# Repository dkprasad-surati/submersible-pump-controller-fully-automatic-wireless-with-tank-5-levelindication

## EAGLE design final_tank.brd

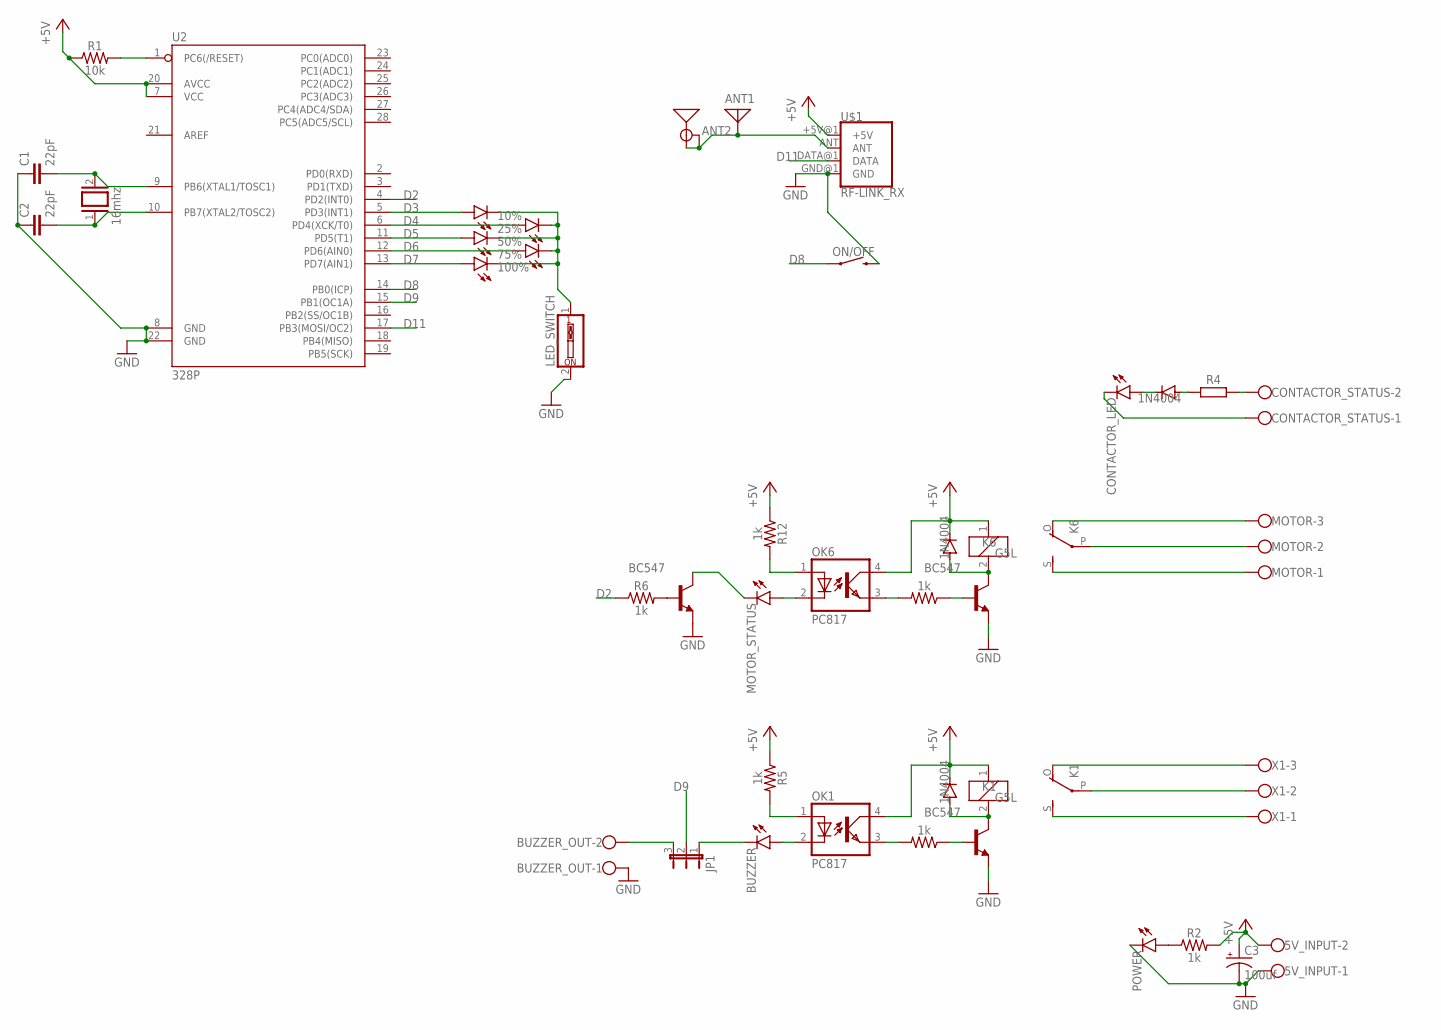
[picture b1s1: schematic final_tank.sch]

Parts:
5V_INPUT: W237-102
10%, 25%, 50%, 75%, 100%: LED3MM
ANT1: ANTENNA; PAD-01
ANT2: ANTENNA-GROUNDEDTRACE-15.2MM; TRACE_ANTENNA_2.4GHZ_15.2MM
BUZZER: LED3MM
BUZZER_OUT: W237-102
C1, C2: 22pF; CAP-PTH-2.54
C3: 100uf; CPOL-RADIAL-5MM-10MM
CONTACTOR_LED: LED3MM
CONTACTOR_STATUS: W237-102
D1, D2, D6: 1N4004; DO41-10
JP1: JP2E; JP2
K1, K6: G5L; G5LE
LED_SWITCH: SW_DIP-1; EDG-01
MOTOR: W237-103
MOTOR_STATUS: LED3MM
OK1, OK6: PC817; DIL04
ON/OFF: MOMENTARY-SWITCH-SPST-PTH-6.0MM; TACTILE_SWITCH_PTH_6.0MM
POWER: LED3MM
Q1: 16mhz; QS
R1: 10k; AXIAL-0.3
R2, R3, R5, R6, R11, R12: 1k; AXIAL-0.3
R4: R_AXIAL-11.7MM-PITCH; RESAD1176W63L850D250B
T1, T2, T6: BC547; TO92
U2: 328P; DIP28
U$1: RF-LINK_RX
X1: W237-103

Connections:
+5V: 5V_INPUT.2, C3.+, R1.P$1 (1), R2.P$2 (2), U2.7 (VCC), U2.20 (AVCC), U$1.+5V@1 (+5V)
D2: R6.P$1 (1), U2.4 (PD2(INT0))
D3: 10%.A, U2.5 (PD3(INT1))
D4: 25%.A, U2.6 (PD4(XCK/T0))
D5: 50%.A, U2.11 (PD5(T1))
D6: 75%.A, U2.12 (PD6(AIN0))
D7: 100%.A, U2.13 (PD7(AIN1))
D8: ON/OFF.1, U2.14 (PB0(ICP))
D9: JP1.2, U2.15 (PB1(OC1A))
D11: U2.17 (PB3(MOSI/OC2)), U$1.DATA@1 (DATA)
GND: 5V_INPUT.1, BUZZER_OUT.1, C1.1, C2.1, C3.-, LED_SWITCH.2, ON/OFF.3 (2), POWER.K (C), T1.1 (E), T2.1 (E), T6.1 (E), U2.8 (GND), U2.22 (GND), U$1.GND@1 (GND)
unnamed: R1.P$2 (2), U2.1 (PC6(/RESET))
unnamed: C1.2, Q1.2, U2.9 (PB6(XTAL1/TOSC1))
unnamed: C2.2, Q1.1, U2.10 (PB7(XTAL2/TOSC2))
unnamed: K6.P, MOTOR.2
unnamed: POWER.A, R2.P$1 (1)
unnamed: D2.C, D6.C, K1.1, K6.1, OK1.4 (COL), OK6.4 (COL), R5.P$1 (1), R12.P$1 (1)
unnamed: D1.A, R4.1
unnamed: CONTACTOR_LED.A, D1.C
unnamed: CONTACTOR_STATUS.2, R4.2
unnamed: CONTACTOR_LED.K (C), CONTACTOR_STATUS.1
unnamed: 10%.K (C), 25%.K (C), 50%.K (C), 75%.K (C), 100%.K (C), LED_SWITCH.1
unnamed: ANT1.1, ANT2.ANT (SIGNAL), ANT2.GND, U$1.ANT
unnamed: D2.A, K1.2, T1.3 (C)
unnamed: R3.P$1 (1), T1.2 (B)
unnamed: OK1.3 (EMIT), R3.P$2 (2)
unnamed: BUZZER.A, OK1.2 (C)
unnamed: OK1.1 (A), R5.P$2 (2)
unnamed: K1.O, X1.3
unnamed: K1.S, X1.1
unnamed: K1.P, X1.2
unnamed: R6.P$2 (2), T2.2 (B)
unnamed: MOTOR_STATUS.K (C), T2.3 (C)
unnamed: BUZZER_OUT.2, JP1.3
unnamed: BUZZER.K (C), JP1.1
unnamed: D6.A, K6.2, T6.3 (C)
unnamed: R11.P$1 (1), T6.2 (B)
unnamed: OK6.3 (EMIT), R11.P$2 (2)
unnamed: MOTOR_STATUS.A, OK6.2 (C)
unnamed: OK6.1 (A), R12.P$2 (2)
unnamed: K6.O, MOTOR.3
unnamed: K6.S, MOTOR.1

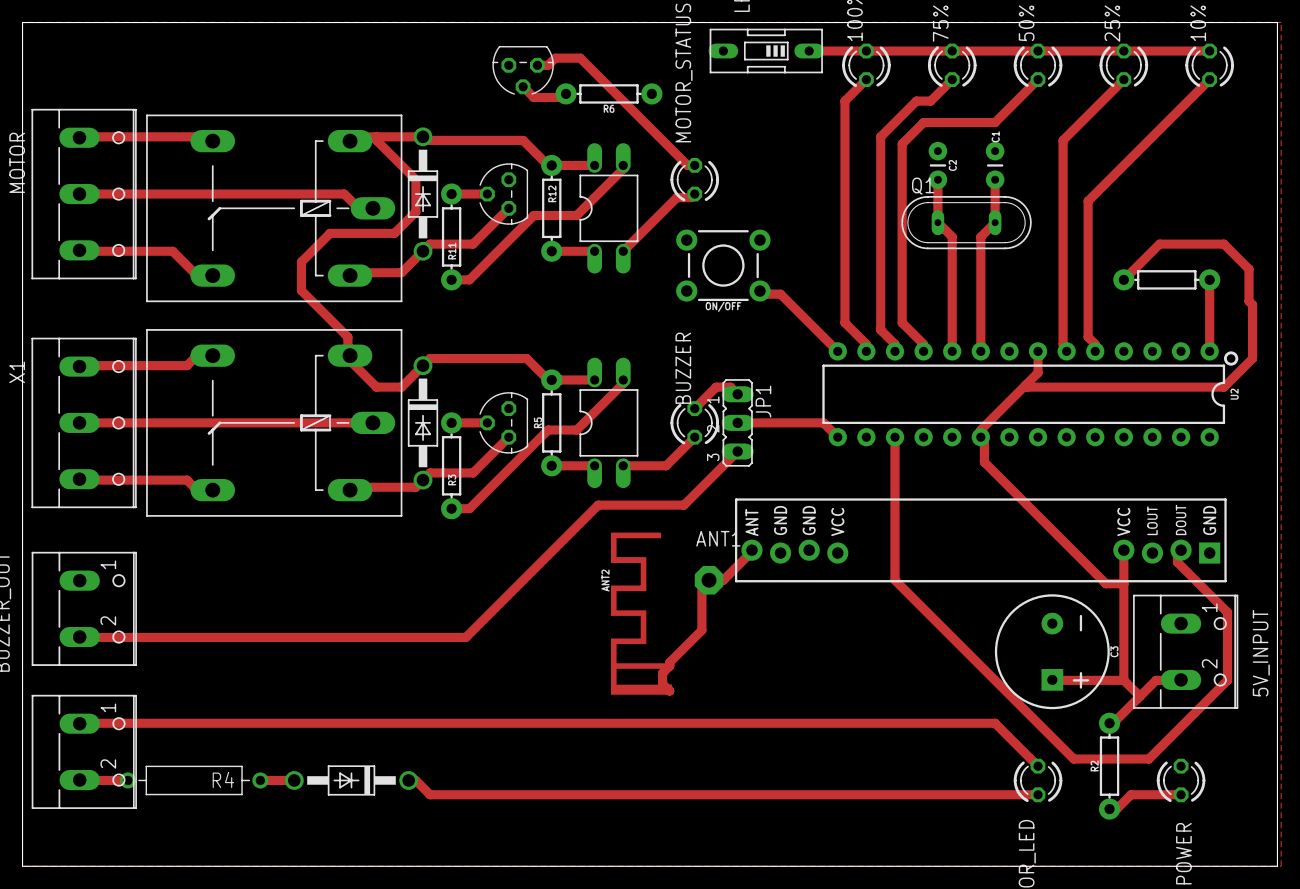
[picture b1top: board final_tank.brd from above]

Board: 2 copper layers, 111.4 x 74.9 mm, 43 parts (0 on the bottom side), 42 nets.

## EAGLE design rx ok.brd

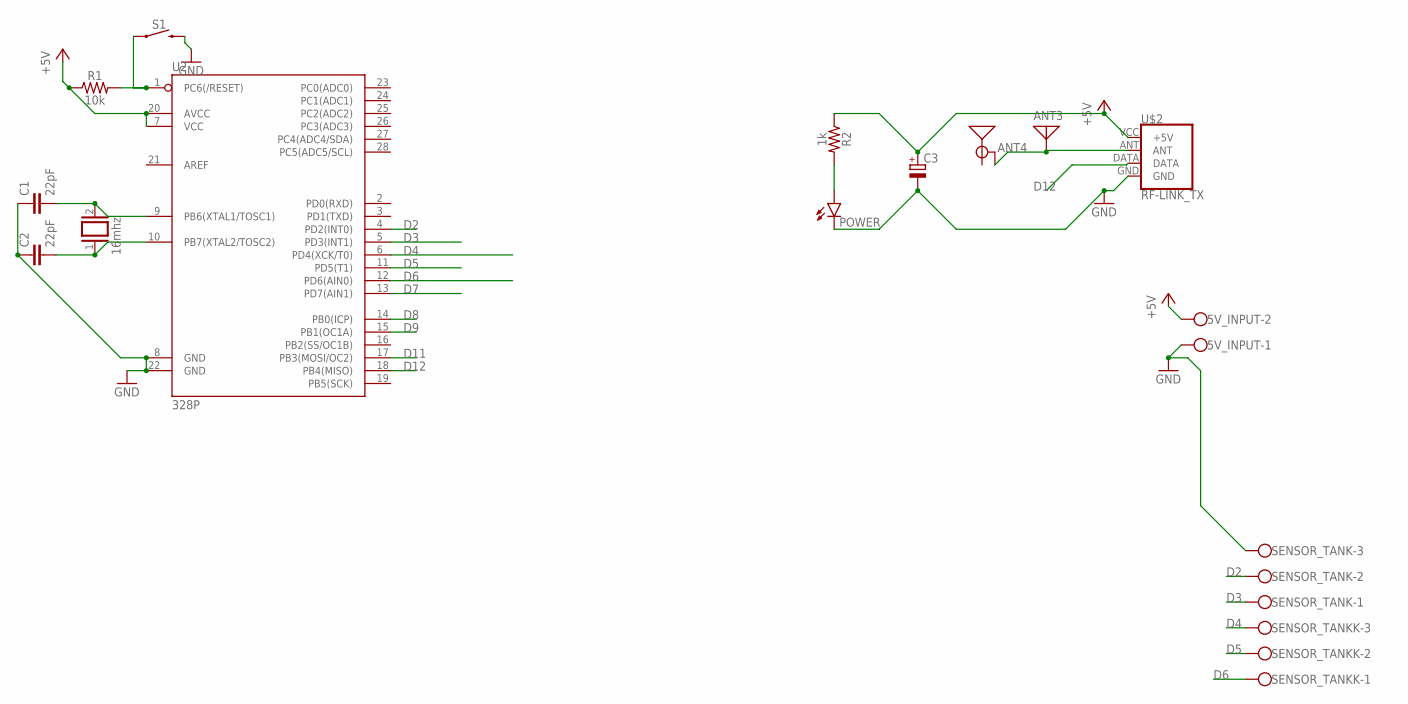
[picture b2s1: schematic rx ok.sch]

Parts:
5V_INPUT: W237-102
ANT3: ANTENNA; PAD-01
ANT4: ANTENNA-GROUNDEDTRACE-15.2MM; TRACE_ANTENNA_2.4GHZ_15.2MM
C1, C2: 22pF; CAP-PTH-2.54
C3: C-POL_RADIAL-20MM-DIA; CAPPRD550W60D1200H2000B
POWER: LED3MM
Q1: 16mhz; QS
R1: 10k; AXIAL-0.3
R2: 1k; AXIAL-0.3
S1: MOMENTARY-SWITCH-SPST-PTH-6.0MM; TACTILE_SWITCH_PTH_6.0MM
SENSOR_TANK: W237-103
SENSOR_TANKK: W237-103
U2: 328P; DIP28
U$2: RF-LINK_TX

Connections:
+5V: 5V_INPUT.2, C3.1 (+), R1.P$1 (1), R2.P$1 (1), U2.7 (VCC), U2.20 (AVCC), U$2.VCC (+5V)
D2: SENSOR_TANK.2, U2.4 (PD2(INT0))
D3: SENSOR_TANK.1, U2.5 (PD3(INT1))
D4: SENSOR_TANKK.3, U2.6 (PD4(XCK/T0))
D5: SENSOR_TANKK.2, U2.11 (PD5(T1))
D6: SENSOR_TANKK.1, U2.12 (PD6(AIN0))
D7: U2.13 (PD7(AIN1))
D8: U2.14 (PB0(ICP))
D9: U2.15 (PB1(OC1A))
D11: U2.17 (PB3(MOSI/OC2))
D12: U2.18 (PB4(MISO)), U$2.DATA
GND: 5V_INPUT.1, C1.1, C2.1, C3.2 (-), POWER.K (C), S1.3 (2), SENSOR_TANK.3, U2.8 (GND), U2.22 (GND), U$2.GND
unnamed: R1.P$2 (2), S1.1, U2.1 (PC6(/RESET))
unnamed: C1.2, Q1.2, U2.9 (PB6(XTAL1/TOSC1))
unnamed: C2.2, Q1.1, U2.10 (PB7(XTAL2/TOSC2))
unnamed: ANT3.1, ANT4.GND, U$2.ANT
unnamed: POWER.A, R2.P$2 (2)

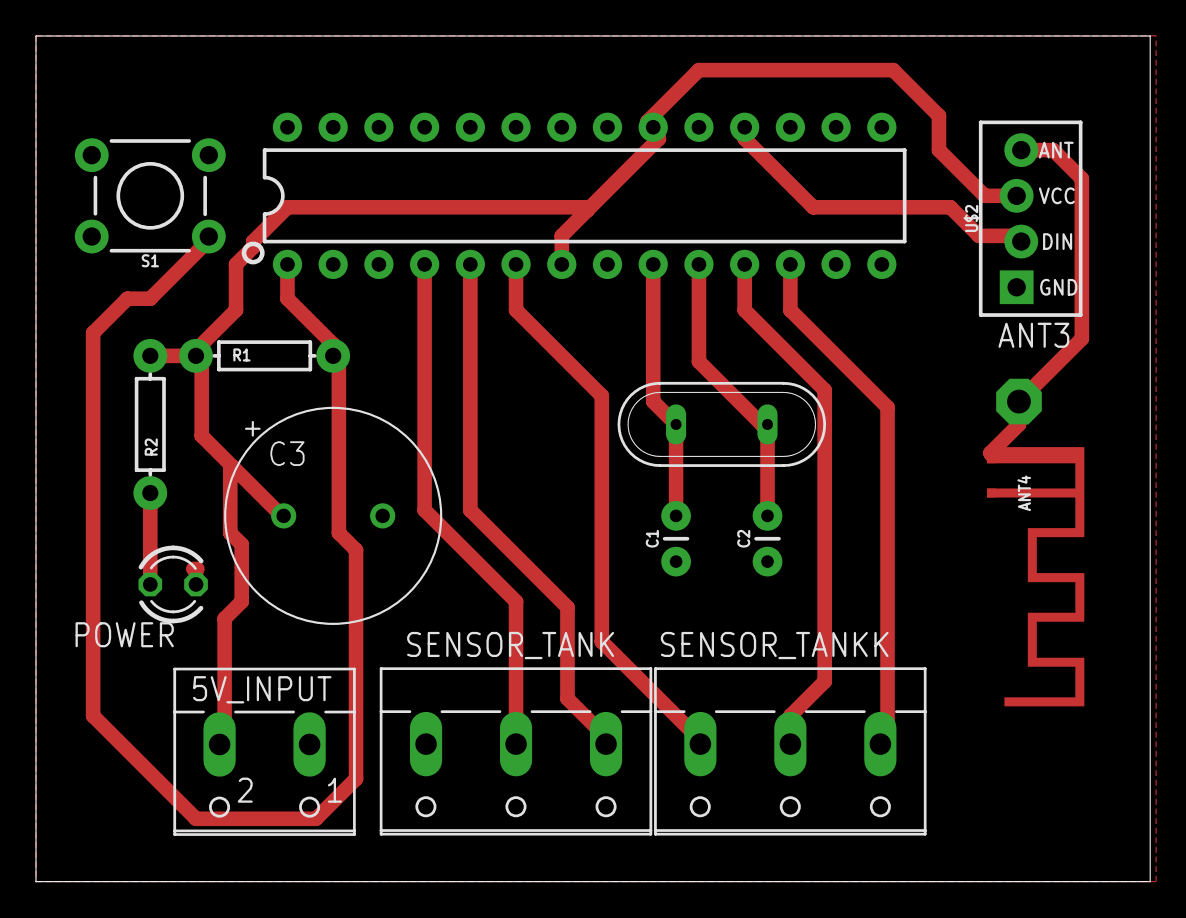
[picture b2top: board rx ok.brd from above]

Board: 2 copper layers, 61.9 x 47.0 mm, 15 parts (0 on the bottom side), 13 nets.

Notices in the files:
parts and their libraries:
SparkFun-IC-Microcontroller: Licensing: Creative Commons ShareAlike 4.0 International - https://creativecommons.org/licenses/by-sa/4.0
